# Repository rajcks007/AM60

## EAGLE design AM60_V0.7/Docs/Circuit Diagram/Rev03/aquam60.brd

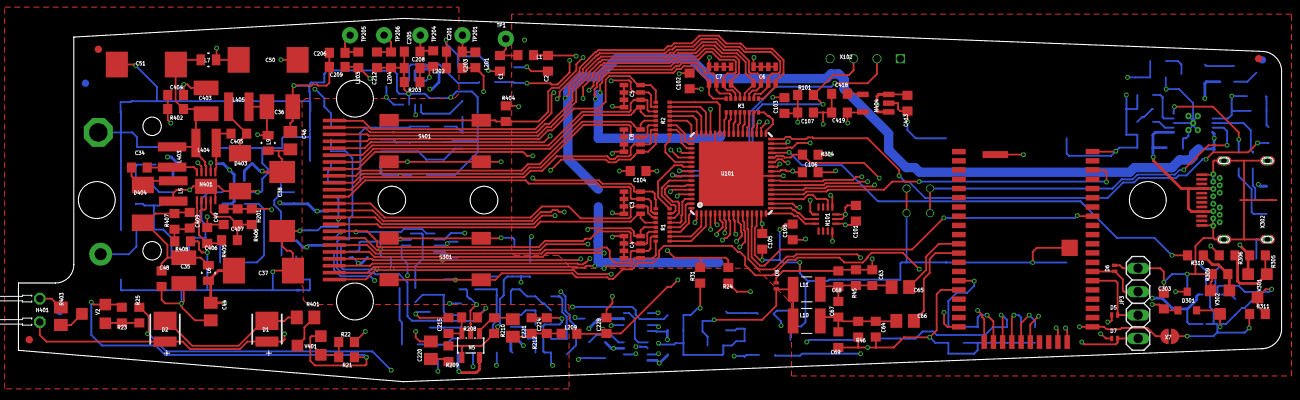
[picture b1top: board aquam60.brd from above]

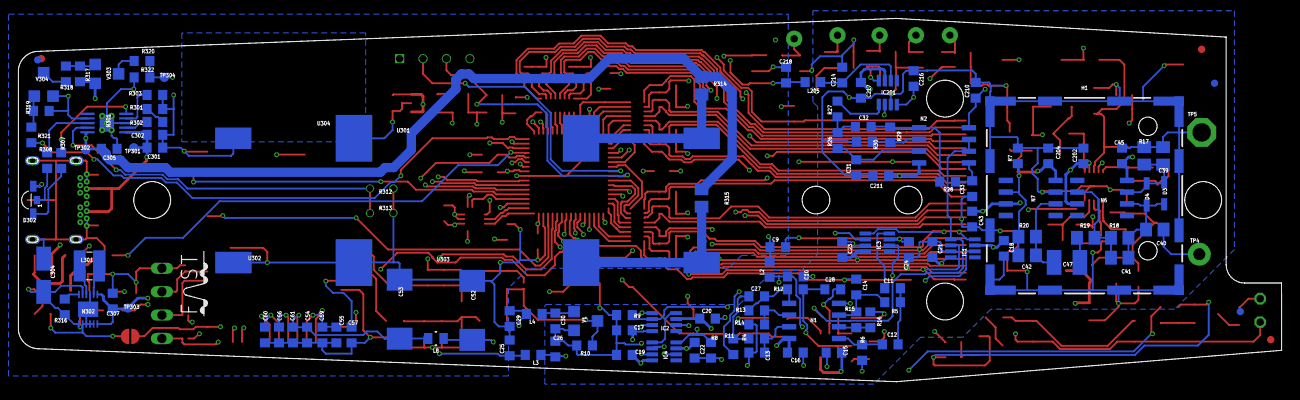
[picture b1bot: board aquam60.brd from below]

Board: 6 copper layers, 137.0 x 39.4 mm, 267 parts (130 on the bottom side), 180 nets.

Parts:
C1, C2, C9, C10, C25, C26, C29, C30, C201, C203, C205, C206, C208, C209, C212, C214, C215, C218, C224, C228: 1n; C0603
C3, C4, C5, C6, C7, C8: 4x10nF; C0612
C11, C12, C14: 27n; C0603
C13: 1n5; C0603
C15, C16, C17, C18, C19, C20, C21, C22, C23, C24, C43, C45, C54, C55, C56, C60, C68, C69, C101, C103, C104, C105, C106, C107, C108, C202, C204, C210, C211, C216, C217, C303, C307, C404: 100n; C0603
C27, C28: 150n; C0603
C31: 16p; C0603
C32, C33: 1n6; C0603
C34, C301, C302, C305, C405, C419: 2u2; C0603
C35, C36: 10u; C1210
C37, C38, C50, C51, C52, C53: 875015119003; WE_WCAP-PHGP
C39, C40, C221: 100n; C0805
C41: 470p; C0805
C42: 100p; C0805
C44, C46, C220: 4u7; C0805
C47: 22u / 25V; C1210
C48, C49, C418: 10n; C0603
C57, C59, C61, C413: 1u; C0603
C63, C64: 470p; C0603
C65, C66: 10u; C0805
C67: 220n; C0603
C102: 4u7; C0603
C304: 865080140004; 2.6X1.6X1(BXCXA)
C403: 47u/16V; C1210
C406: 1uF; C0603
C407, C409: 100p; C0603
D1, D2: 158303240A; WL-SWTP_3030
D3, D4: 1N4448WS-7-F; SOD-323
D5, D6, D7, D8: PESD5V0X1BL,315; DIODFN100X60X60-2
D301: BAT54C; SOT23
D302: 155124RG73200; WL-SBSW_1204
D403, D404: B240A; DO214AC
H1: 36103205; WE-SHC_SMD-FRAME_36103205
H201: AQUAM60
H401: LL-304WC2E-W2-3TC; LED3MM_H7,5MM
IC1, IC2, IC3, IC4, IC201: TS12A12511DCNR; SOT-23-8
JP3: n.b.; 1X04
L1, L2, L3, L4, L202, L205, L209: 742863160; R0603
L5, L403, L404, L405: 744025100; WE-TPC_2811/2813
L6, L7, L8, L9: 100nH; WE-KI_0805
L10, L11: LQW32FT220M0HL; INDC3225X250N
L201, L203, L204: 742792602; R0603
L301: 74438336022; WE-MAPI_3015/3020
M1: BM83SM1; BM83
N1, N2: TL082IDR; SO-8
N5: TLV170IDBV; SOT-23L
N6: LF356M; SO-8
N7: OP27GS; SO-8
N101: LSM6DSL; LGA-14
N301: BQ24092; HVSSOP10
N302: LM3668SD-4550/NOPB; DFN_12POL_+0,2MM
N401: LT3471EDD; DFN_10POL_3X3MM+0,2MM
N404: TPS79933DDCR; SOT-23-5
R1, R2, R3: 8x10K; R1506
R4: 330k; R0603
R5: 6k8; R0603
R6, R305, R309, R317, R319, R404: 22k; R0603
R7, R21, R23, R45, R46, R101, R203, R320, R402, R405: 10k; R0603
R8: 12k; R0603
R9, R10, R210: 100k; R0603
R11, R12, R27: 3k3; R0603
R13, R15, R24, R29, R31: 0; R0603
R14, R16, R30: n.b.; R0603
R17: 100k; R0805
R18: 10M; R0805
R19: 1k; R0805
R20: 150k; R0805
R22, R25, R208, R301, R302, R304, R306, R308, R310, R318, R321: 1k; R0603
R26: 3M3; R0603
R28: 33k; R0603
R209: 4k7; R0603
R212: 68k; R0603
R303: 3k9; R0603
R307: 5k6; R0603
R311: 180k; R0603
R312, R313: 203AT-2; AT-2
R314, R315: 0ZCK0100FF2E; R0805
R316: 10M; R0603
R322: 2k7; R0603
R401: 470R; R0805
R403: 47R; R0805
R406: 51k; R0603
R407: 160k; R0603
R408: 39k; R0603
S301, S401: 1301.9320; 1301.93XX
TP1, TP201, TP204, TP205, TP206: n.b.; P1-08
TP4: n.b.; P1-13R
TP5: n.b.; P1-20
TP301, TP302, TP303, TP304: n.b.; TP10R
U101: ATXMEGA64A3-MH; MLF-(VQFN)-64M2-64
U301, U303: 55; 55+
U302, U304: 55; 55-
U$1: LOGO_KLEIN
U$2, U$3, U$5, U$6, U$7, U$8: PASSER-CIRCLE-0.8MM
V1, V2, V302, V304, V401: FDV301N; SMDTR-1
V301, V303: NTR2101PT1G; SMDTR-1
X7: n.b.; LöTBRüCKE_2
X102: n.b.; AVRPDI4
X302: 632 723 300 011; 632723300011_4L

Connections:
1A: R3.12, U101.37
1B: R3.10, U101.38
1C: R3.8, U101.39
1D: R3.6, U101.40
1E: R3.4, U101.41
1F: R3.2, U101.42
1G: R2.16, U101.43
2A: R2.12, U101.47
2B: R2.10, U101.48
2C: R2.8, U101.49
2D: R2.6, U101.50
2E: R2.4, U101.51
2F: R2.2, U101.54
2G: R1.16, U101.55
!INT1!_PC2: N101.4, U101.18
!INT2!_PC3: N101.9, U101.19
!SS!_PE0: N101.12, U101.30
+4.1V: C305.1, D302.2, N301.10, R305.2, R314.2, R315.2, R317.2, TP302.TP, V301.2, V303.2
+4V5: C50.2+, C307.2, C413.1, D1.2, D2.2, H401.A, L7.1, N302.1, N302.12, N404.1, N404.3, TP303.TP
+5V: C15.2, C17.2, C19.2, C21.2, C23.2, C37.2+, C43.1, C44.1, C202.2, C203.1, C210.2, C216.2, IC1.4, IC2.4, IC3.4, IC4.4, IC201.4, L6.2, L201.2, N1.8, N2.8, N5.5, N6.7, N7.7
-5V: C16.1, C18.1, C20.1, C22.1, C24.1, C38.1-, C45.2, C46.2, C204.1, C209.1, C211.1, C217.1, IC1.7, IC2.7, IC3.7, IC4.7, IC201.7, L9.2, L203.2, N1.4, N2.4, N6.4, N7.4
ADAP_IN: C55.2, C59.2, D7.1, JP3.1, M1.22
ADC3: C228.1, L209.2, U101.1
ADC7: R320.1, R322.2, TP304.TP, U101.5
AGND: C1.2, C10.2, C13.1, C15.1, C16.2, C17.1, C18.2, C19.1, C20.2, C21.1, C22.2, C23.1, C24.2, C26.2, C28.1, C30.2, C31.1, C33.1, C35.2, C36.1, C37.1-, C38.2+, C39.2, C43.2, C44.2, C45.1, C46.1, C48.2, C49.1, C51.1-, C201.2, C202.1, C203.2, C204.2, C205.2, C206.2, C208.2, C209.2, C210.1, C211.2, C212.2, C214.2, C215.2, C216.1, C217.2, C220.1, C224.2, C403.2, C404.2, C406.2, D403.C, H1.1, H1.2, H1.3, H1.4, H1.5, H1.6, H1.7, H1.8, H1.9, H1.10, H1.11, H1.12, H1.13, H1.14, H1.15, H1.16, IC1.3, IC2.3, IC3.3, IC4.3, IC201.3, L5.1, L204.2, N5.2, N7.3, N401.5, N401.11, R6.1, R7.2, R8.2, R9.2, R10.2, R14.1, R16.1, R17.1, R30.1, R31.1, R203.2, R212.1, R408.1, TP5.TP, V1.2
AIL: C66.1, M1.12
AIR: C65.1, M1.11
B0: R1.10, U101.62
B1: R1.8, U101.63
B2: R1.6, U101.64
B3: R1.4, U101.2
B4: R1.2, U101.3
CLK_PC1: N101.13, U101.17
COM: R2.14, U101.46
DM: D5.1, JP3.2, M1.36
DP: D6.1, JP3.3, M1.37
GND: C2.2, C3.2, C3.4, C3.6, C3.8, C4.2, C4.4, C4.6, C4.8, C5.2, C5.4, C5.6, C5.8, C6.1, C6.3, C6.5, C6.7, C7.1, C7.3, C7.5, C7.7, C8.1, C8.3, C8.5, C8.7, C9.2, C25.2, C29.2, C50.1-, C52.1-, C53.1-, C54.1, C55.1, C56.1, C57.1, C59.1, C60.1, C61.1, C63.2, C64.1, C68.2, C69.1, C101.2, C102.2, C103.2, C104.2, C105.2, C106.2, C107.2, C108.2, C218.2, C228.2, C301.2, C302.2, C303.1, C304.2, C305.2, C307.1, C413.2, C418.2, C419.2, D5.2, D6.2, D7.2, D8.2, JP3.4, M1.16, M1.50, M1.56, M1.57, N101.6, N101.7, N301.3, N301.7, N301.11, N301.P$1, N301.P$2, N301.P$3, N301.P$4, N301.P$5, N302.3, N302.8, N302.9, N302.10, N302.11, N302.13, N404.2, R21.1, R23.1, R24.2, R31.2, R45.1, R46.2, R301.1, R303.1, R309.1, R311.1, R312.P$1, R313.P$1, R319.1, R322.1, S301.P1, S301.P2, S401.P1, S401.P2, U101.14, U101.24, U101.34, U101.44, U101.52, U101.60, U101.TH, U302.P$1, U302.P$2, U304.P$1, U304.P$2, V2.2, V302.2, V304.2, V401.2, X7.1, X102.4, X302.A1, X302.A12, X302.B1, X302.B12, X302.G3, X302.G4, X302.Z1, X302.Z2, X302.Z3, X302.Z4, X302.Z5, X302.Z6
MICBIAS: C57.2, M1.15
unnamed: H401.K, R403.2
unnamed: C51.2+, C403.1, L7.2, L403.1, L404.1, N401.8, R402.2
unnamed: C10.1, IC3.6, IC4.6, L2.1
unnamed: R401.1, V401.3
unnamed: D302.3, R307.1
unnamed: D302.1, R308.1
unnamed: N301.8, R308.2
unnamed: C1.1, L1.1, TP1.TP
unnamed: IC1.2, IC2.2, R9.1
unnamed: D1.1, D2.1, R401.2
unnamed: C208.1, IC201.8, L202.2, R203.1
unnamed: IC1.8, IC3.1
unnamed: C205.1, L202.1, TP204.TP
unnamed: C214.1, IC201.6, L205.1
unnamed: N5.4, R209.2, R210.2
unnamed: C26.1, IC1.6, IC2.6, L3.1
unnamed: C201.1, L201.1, TP201.TP
unnamed: C221.2, N5.1, R210.1
unnamed: C4.1, H201.P$7, R1.7
unnamed: C220.2, R209.1
unnamed: C215.1, N5.3, R208.1
unnamed: R314.1, U301.P$1, U301.P$2
unnamed: C304.1, N302.5, N302.7, R311.2, R316.1, V301.3
unnamed: C32.1, R26.2, R27.1
unnamed: C36.2, C49.2, C407.2, L9.1, L405.2, R406.1
unnamed: D301.3, S301.P3, S301.P4
unnamed: C31.2, N2.3, R26.1
unnamed: C418.1, N404.4
unnamed: C33.2, N2.5, R28.1
unnamed: C63.1, C65.2, C67.2, C68.1, L11.2, R45.2
unnamed: U101.56, X102.2
unnamed: R101.1, U101.57, X102.3
unnamed: R318.1, V304.3
unnamed: R317.1, R318.2, V303.1
unnamed: R319.2, R321.2, V304.1
unnamed: C301.1, C302.1, N301.1, TP301.TP, X302.A4, X302.A9, X302.B4, X302.B9
unnamed: N301.2, R302.2
unnamed: R320.2, V303.3
unnamed: N301.4, R303.2
unnamed: C221.1, C224.1, L209.1, R212.2
unnamed: N301.9, R312.P$2, R313.P$2
unnamed: IC2.8, IC4.1
unnamed: C27.1, R4.2, R11.1
unnamed: N301.5, R307.2
unnamed: N302.6, R316.2
unnamed: C13.2, N1.3, R4.1
unnamed: C212.1, L204.1, TP206.TP
unnamed: C35.1, C48.1, C409.1, D404.C, L6.1, R407.2
unnamed: R21.2, R22.1, V401.1
unnamed: R305.1, R306.2, V301.1
unnamed: L301.1, N302.4
unnamed: D301.2, R306.1, V302.3
unnamed: R309.2, R310.2, V302.1
unnamed: R23.2, R25.2, V2.1
unnamed: C32.2, N2.1, R28.2, R29.1
unnamed: N1.2, R13.2, R14.2
unnamed: L301.2, N302.2
unnamed: C206.1, L203.1, TP205.TP
unnamed: R315.1, U303.P$1, U303.P$2
unnamed: R301.2, R302.1
unnamed: C6.2, H201.P$22, R3.9
unnamed: C6.4, H201.P$23, R3.11
unnamed: C6.6, H201.P$11, R3.13
unnamed: C6.8, H201.P$10, R3.15
unnamed: C7.2, H201.P$24, R3.1
unnamed: C7.4, H201.P$2, R3.3
unnamed: C7.6, H201.P$3, R3.5
unnamed: C7.8, H201.P$4, R3.7
unnamed: C8.2, H201.P$20, R2.1
unnamed: C8.4, H201.P$14, R2.3
unnamed: C8.6, H201.P$15, R2.5
unnamed: C8.8, H201.P$16, R2.7
unnamed: C27.2, N1.1, R12.2, R13.1
unnamed: C28.2, IC4.2, R12.1
unnamed: IC3.2, R11.2
unnamed: C11.2, IC3.8
unnamed: C11.1, C12.1, R5.1
unnamed: C12.2, N1.5, R6.2
unnamed: C14.1, N1.7, R5.2, R15.1
unnamed: C14.2, IC4.8, R8.1
unnamed: C30.1, L4.1, V1.1
unnamed: C404.1, N401.7, N401.9, R402.1
unnamed: IC201.1, R27.2
unnamed: C405.2, L404.2, N401.6
unnamed: R403.1, V2.3
unnamed: C405.1, D403.A, L405.1
unnamed: C34.2, L403.2, N401.10
unnamed: C34.1, D404.A, L5.2
unnamed: N2.2, R29.2, R30.2
unnamed: N1.6, R15.2, R16.2
unnamed: C39.1, D3.A, D4.K, N6.3, R17.2
unnamed: C64.2, C66.2, C67.1, C69.2, L10.2, R46.1
unnamed: C40.2, C41.1, D3.K, D4.A, N6.2, R18.2
unnamed: C41.2, N6.6, R18.1, R19.2
unnamed: C42.1, C47.2, N7.2, R20.2
unnamed: C42.2, IC201.2, N7.6, R7.1, R20.1
unnamed: C3.1, H201.P$17, R1.15
unnamed: C47.1, R19.1
unnamed: C40.1, TP4.TP
unnamed: C3.3, H201.P$13, R1.13
unnamed: C3.5, H201.P$12, R1.11
unnamed: C5.1, H201.P$21, R2.15
unnamed: C4.3, H201.P$8, R1.5
unnamed: C4.5, H201.P$6, R1.3
unnamed: C4.7, H201.P$5, R1.1
unnamed: C3.7, H201.P$9, R1.9
unnamed: C5.3, H201.P$1, R2.13
unnamed: C5.5, H201.P$19, R2.11
unnamed: C5.7, H201.P$18, R2.9
unnamed: C409.2, N401.1, R407.1, R408.2
unnamed: C407.1, N401.4, R405.1, R406.2
unnamed: C406.1, N401.2, N401.3, R405.2
NF1: IC1.1, N2.6, N2.7, R208.2
NF2: D8.1, IC2.1, L10.1, L11.1, R10.1, V1.3
P2_6: M1.21, U101.6
P3_2: M1.20, U101.9
P3_4_UART_RTS: M1.31, U101.21, X7.2
P3_7_UART_CTS: M1.48, U101.20
P8_5_UART_TXD: M1.30, U101.22
P8_6_UART_RXD: M1.29, U101.23
PA4: R321.1, U101.32
PA6: C218.1, L205.2, U101.11
PB1: C9.1, L2.2, U101.7
PD0: C29.1, L4.2, U101.26
PD1: R22.2, U101.27
PD2: C303.2, D301.1, R304.1, U101.28
PD3: R310.1, U101.29
PD5: R25.1, U101.31
PD7: C25.1, L3.2, U101.12
PWR: M1.26, U101.4
RST_N: M1.43, U101.13
SDA_PC0: N101.14, U101.16
SENSOR: C2.1, L1.2, U101.10
SYS_PWR: C56.2, M1.24
T1: R3.16, U101.33
T2: R3.14, U101.36
T3: R1.14, U101.58
T4: R1.12, U101.59
TAST2: R404.1, S401.P3, S401.P4, U101.8
VCC: C52.2+, C101.1, C102.1, C103.1, C104.1, C105.1, C106.1, C107.1, C108.1, C419.1, L8.1, N101.5, N101.8, N404.5, R101.2, R304.2, R404.2, U101.15, U101.25, U101.35, U101.45, U101.53, U101.61, X102.1
VDD: C53.2+, C54.2, C61.2, L8.2, M1.23
VDD_IO: C60.2, M1.25

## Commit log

2024-11-04 working

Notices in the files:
parts and their libraries:
Eagle_COLOR_LED: Copyright: Würth Elektronik
